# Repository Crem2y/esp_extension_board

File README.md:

# ESP Extension Board

- IOT Extension board for `LOLIN D1 mini`(ESP8266) / `ESP32C3 SuperMini`
- Tool : Kicad 9.0
# Pinout

|  Connector   | ESP8266 | ESP32C3 |
|--------------|---------|---------|
| 0 (J6)       | GPIO16  | GPIO0   |
| 1 (J7)       | GPIO5   | GPIO1   |
| 2 (J8)       | GPIO4   | GPIO2   |
| 3 (J9)       | GPIO0   | GPIO3   |
| 4 (J10)      | GPIO2   | GPIO4   |
| 5 (J11)      | GPIO14  | GPIO5   |
| 6 (J12)      | GPIO12  | GPIO6   |
| 7 (J13, DHT) | GPIO13  | GPIO7   |
| 8 (J5)       | GPIO15  | GPIO8   |

# schematics

# PCB

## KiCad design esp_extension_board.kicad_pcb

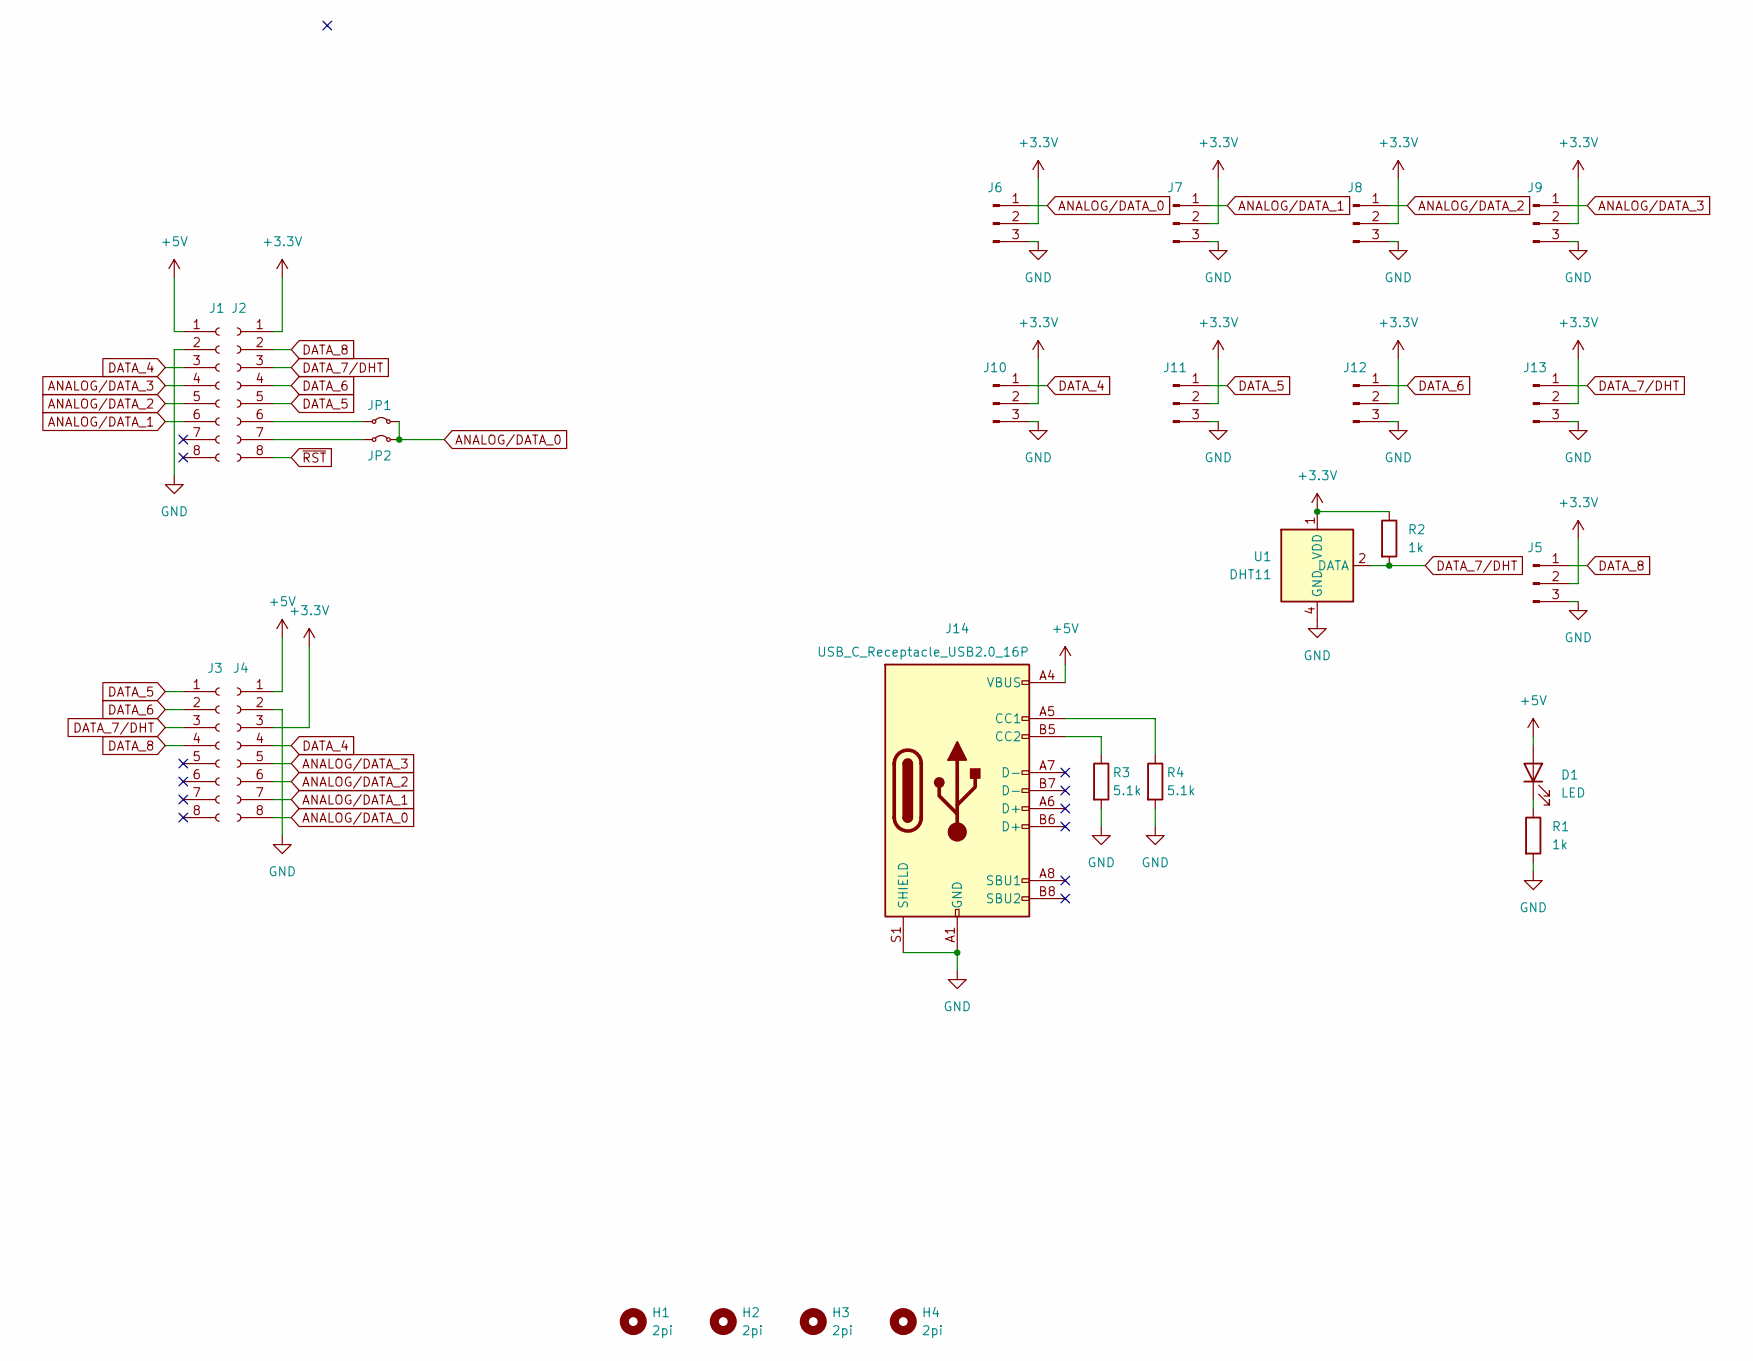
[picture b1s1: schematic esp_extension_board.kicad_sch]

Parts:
D1: LED; LED_0805_2012Metric_Pad1.15x1.40mm_HandSolder
H1, H2, H3, H4: 2pi; MountingHole_2mm
J1, J2, J3, J4: Conn_01x08_Socket; PinSocket_1x08_P2.54mm_Vertical
J5, J6, J7, J8, J9, J10, J11, J12, J13: Conn_01x03_Pin; Molex_SPOX_5267-03A_1x03_P2.50mm_Vertical
J14: USB_C_Receptacle_USB2.0_16P; USB_C_Receptacle_XKB_U262-16XN-4BVC11
JP1, JP2: Jumper_2_Small_Bridged; SolderJumper-2_P1.3mm_Bridged_RoundedPad1.0x1.5mm
R1, R2: 1k; R_0805_2012Metric_Pad1.20x1.40mm_HandSolder
R3, R4: 5.1k; R_0805_2012Metric_Pad1.20x1.40mm_HandSolder
U1: DHT11; ASAIR_AM2302_P2.54mm_Lead2.75mm_TabDown

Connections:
+3.3V: J2.1, J4.3, J5.2, J6.2, J7.2, J8.2, J9.2, J10.2, J11.2, J12.2, J13.2, R2.1, U1.1 (VDD)
+5V: D1.2 (A), J1.1, J4.1, J14.A4 (VBUS), J14.A9 (VBUS), J14.B4 (VBUS), J14.B9 (VBUS)
ANALOG/DATA_0: J4.8, J6.1, JP1.2 (B), JP2.2 (B)
ANALOG/DATA_1: J1.6, J4.7, J7.1
ANALOG/DATA_2: J1.5, J4.6, J8.1
ANALOG/DATA_3: J1.4, J4.5, J9.1
DATA_4: J1.3, J4.4, J10.1
DATA_5: J2.5, J3.1, J11.1
DATA_6: J2.4, J3.2, J12.1
DATA_7/DHT: J2.3, J3.3, J13.1, R2.2, U1.2 (DATA)
DATA_8: J2.2, J3.4, J5.1
GND: J1.2, J4.2, J5.3, J6.3, J7.3, J8.3, J9.3, J10.3, J11.3, J12.3, J13.3, J14.A1 (GND), J14.A12 (GND), J14.B1 (GND), J14.B12 (GND), J14.S1 (SHIELD), R1.2, R3.2, R4.2, U1.4 (GND)
unnamed: D1.1 (K), R1.1
unnamed: J2.6, JP1.1 (A)
unnamed: J2.7, JP2.1 (A)
unnamed: J14.A5 (CC1), R4.1
unnamed: J14.B5 (CC2), R3.1
~RST: J2.8

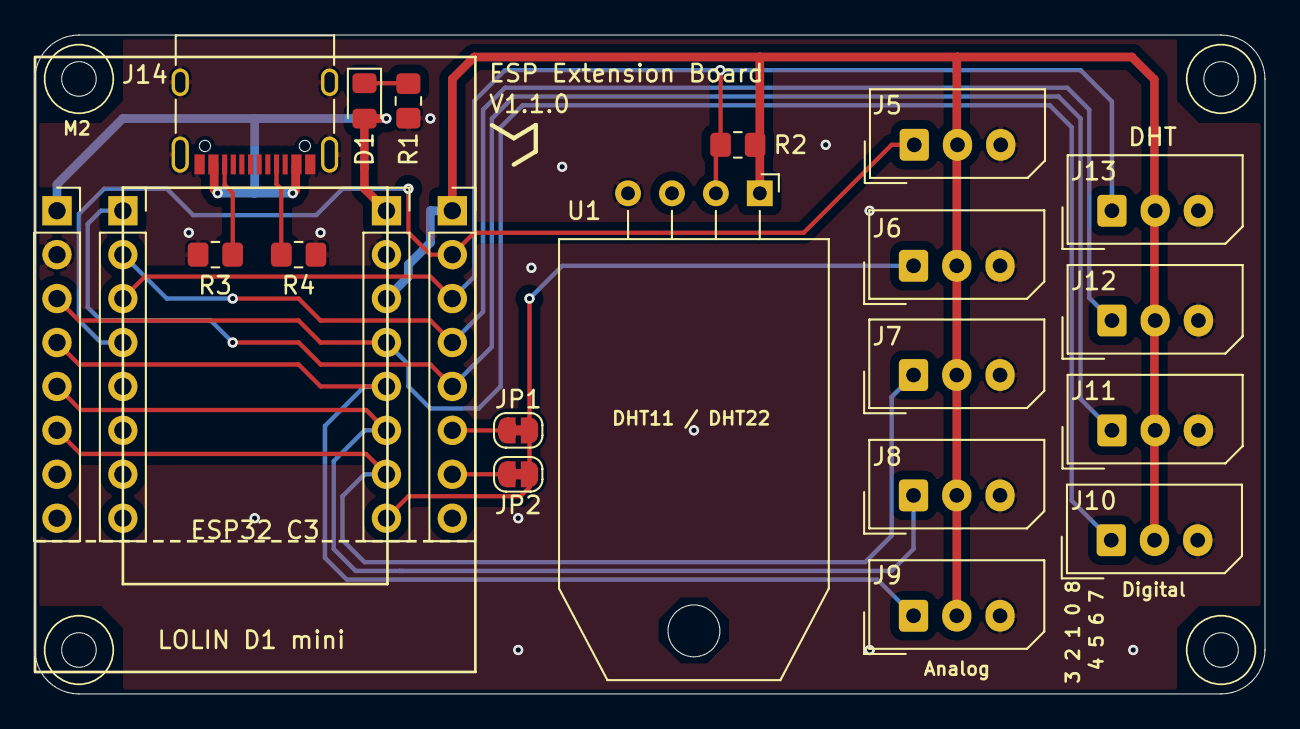
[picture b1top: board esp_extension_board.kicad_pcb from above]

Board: 2 copper layers, 71.1 x 38.1 mm, 26 parts (0 on the bottom side), 17 nets.
